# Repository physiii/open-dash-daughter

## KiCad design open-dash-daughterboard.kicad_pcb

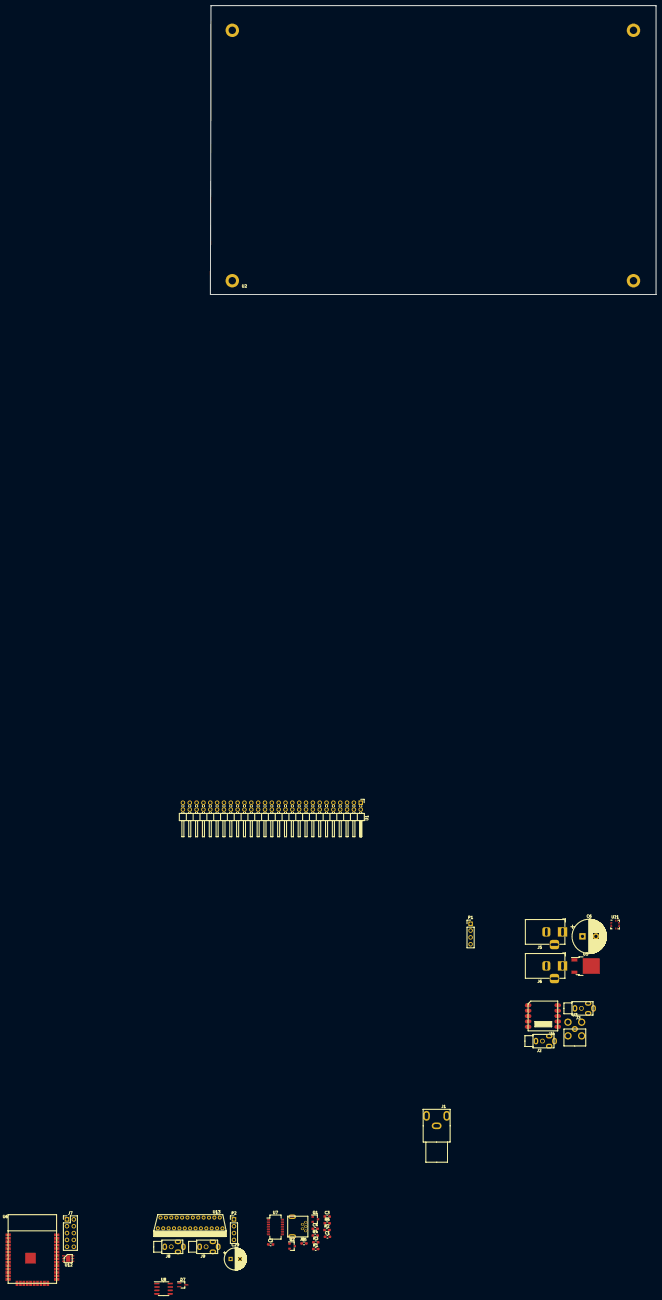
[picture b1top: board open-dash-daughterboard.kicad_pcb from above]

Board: 2 copper layers, 165.5 x 107.3 mm, 37 parts (0 on the bottom side), 41 nets, no tracks yet.

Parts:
C1, C2: C_47pF; C_0603_1608Metric_Pad1.05x0.95mm_HandSolder
C3, C5: C_0.1uF; C_0603_1608Metric_Pad1.05x0.95mm_HandSolder
C4: C_4.7uF; C_0603_1608Metric_Pad1.05x0.95mm_HandSolder
C6: C_1000uF; CP_Radial_D12.5mm_P5.00mm
C29: 470uF; CP_Radial_D8.0mm_P3.50mm
D7: PESD1CAN; SOT-323_SC-70_Handsoldering
J1: RCA-PJRAN1X1U04X
J2, J3, J8, J9: AudioJack4_TTRS; AudioConn-SJ1-2503A
J4: USB_MINI_B; USB-mini-B-0548190519
J5, J6: Barrel_Jack_OD5.5_ID2.5; BarrelJack_OD5.5_ID2.5
J7: Conn_02x05_Odd_Even; PinHeader_2x05_P2.54mm_Vertical
P1, P2: CONN_01X04; PinHeader_1x04_P2.54mm_Vertical
Q1: Q_NPN_BCE; SOT-23
Q2: Q_PNP_BCE; SOT-23
R1, R2: R_27; R_0603_1608Metric_Pad1.05x0.95mm_HandSolder
R3, R4: R_10k; R_0603_1608Metric_Pad1.05x0.95mm_HandSolder
R6: R_4K7; R_0603_1608Metric_Pad1.05x0.95mm_HandSolder
U1: TE-AUTO-CONN-52; PinHeader_2x27_P2.54mm_Horizontal
U2: radio-housing-mounts
U3: ANTENNA-COAX-AUTO; ANTENNA-AUTO- 638817-4
U4: RDA5807M
U5: REG-3.3v; TO-252-2
U6: ESP-WROOM-32
U7: FT231XS; SSOP-20_3.9x8.7mm_P0.635mm
U8: MCP2551-I_SN; SOIC-8_3.9x4.9mm_P1.27mm
U12: SI7020-A20
U13: TDA7851F; Flexiwatt25-V
U?1: ACS711; ACS711KEXLT-15AB-T

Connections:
/3V3: P1.2, U4.5, U5.2, U6.2, U12.5, U?1.12
/5V: C4.1, C5.1, P1.3, U5.3, U7.15, U8.3
/BATTERY: C6.1, C29.2, P1.4, U1.44, U?1.1
/CAMERA+: J1.2, J1.3, U1.31
/CAMERA-: J1.1, U1.32
/CAN+: D7.2, U1.2, U8.7
/CAN-: D7.1, U1.12, U8.6
/CAN_RX: U6.26, U6.28, U8.4
/CAN_TX: U6.29, U8.1
/FM Radio/AMF_Antenna: J3.2, J3.3, U3.1, U4.8
/FM Radio/L_FM: J2.2, J2.3, U4.7
/LF+: U1.47, U13.9
/LF-: U1.51, U13.7
/LR+: U1.48, U13.17
/LR-: U1.52, U13.19
/PROG: J7.3, Q2.2, U6.25
/RF+: U1.46, U13.5
/RF-: U1.50, U13.3
/RR+: U1.45, U13.21
/RR-: U1.49, U13.23
/RXD: J7.2, U6.34, U7.4
/SCL: J7.6, U4.2, U6.33, U12.6
/SDA: J7.8, U4.1, U6.31, U12.1
/TXD: J7.4, U6.35, U7.20
/USB interface/3V3OUT: C3.1, U7.3, U7.14
/USB interface/DTR: Q2.3, R4.2, U7.1
/USB interface/RTS: Q1.3, U7.2
/USB interface/USBDM: C1.1, J4.3, R1.2
/USB interface/USBDP: C2.1, J4.2, R2.2
/USB interface/VBUS: J4.1, R6.2
/USB interface/VSENSE: R6.1, U7.18
/audio amplifier/IN1: J8.2, J8.3, P2.4
/audio amplifier/IN2: J8.4, P2.3
/audio amplifier/IN3: J9.2, J9.3, P2.2
/audio amplifier/IN4: J9.4, P2.1
/microcontroller/FACT: J7.5, U6.13
/microcontroller/SOFT_POWER: J7.1, U6.14
GND: C1.2, C2.2, C3.2, C4.2, C5.2, C6.2, C29.1, D7.3, J2.1, J3.1, J3.4, J4.5, J5.2, J5.3, J6.2, J6.3, J7.9, J7.10, J8.1, J9.1, P1.1, U1.33, U1.43, U3.2, U4.6, U5.1, U6.1, U7.6, U7.16, U8.2, U12.2, U13.1, U13.13, U?1.5
unnamed: Q2.1, R3.2
unnamed: R1.1, U7.12
unnamed: R2.1, U7.11

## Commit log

2018-02-08 initial commit, added initial layout and datasheets for esp32 and CM108AH
2018-02-20 added initial layout
2018-02-22 added some libraries
2018-02-23 merged smart regulator with open-dash-daughter
2018-03-22 merged in smart regulator
2018-04-01 rearrange files/dir
2018-04-02 Ethan Initial Commit
    Copy of power section from smart-regulator
2018-04-02 Micro and Environment Schematic Copy
    Copied over the microcontroller and environment sheets from smart-regulator project. Also modified the power section.
2018-04-03 change branch
2018-04-03 Power Schematic Update
    Test commit and minior power schematic update.
2018-04-03 Backup Before SEPIC Design
2018-04-04 Component Updates in Power Section
2018-04-05 Updated Power Schematic
    Power Schematic Updated for 3.3V, 5V, and 8V Buck Regulators. All regulator parts have correct footprints and selected components.
    Prelim orgainization of PCB - grouped parts by section.
2018-04-05 Update Power Schematic and directed parts to open-automation library
    Change 3.3V and 5V buck regulator to adjustable chip version.
    Directed multiple parts from -cache.lib to open-automation.lib.
2018-04-06 Schematic Work on Audio Amp
    Audio amplifier implemented with selected components and footprints.
2018-04-06 Removed Light Sensor from Enviornment Schematic
2018-04-10 updated to v5 kicad
2018-04-12 finished updating libraries
2018-04-12 cleaned up some merge errors
2018-04-12 cleaning up repo
2018-04-12 latest and greatest, started canbus schematic
2018-04-17 added thermometer and switches for programming esp8299/esp32
2018-04-17 minor mods
2018-04-17 added GPS module, GPS will be on a carrier board and will plug into the daughter board.
2018-04-17 Backup before switching to lawrence-test branch
    Schematic library has issues after updating to KiCad V5.
2018-04-18 Revert "Backup before switching to lawrence-test branch"
    This reverts commit 5eeefb6d84a8db9381deb81c77fe1ec3b29fea69.
2018-04-18 Revert "Merge branch 'lawrence_test' into ethan"
    This reverts commit 4dccd689ac590a7d6c1598150e10b9b87c6b396b, reversing
    changes made to 5eeefb6d84a8db9381deb81c77fe1ec3b29fea69.
2018-04-18 Revert "Revert "Merge branch 'lawrence_test' into ethan""
    This reverts commit 6eb6401587b4cfce8c2da15c6df37be90675c3d0.
2018-04-18 Revert "added GPS module, GPS will be on a carrier board and will plug into the daughter board."
    This reverts commit f32f9f36995d7517ca6e5476fe45c3fadeca4b65.
2018-04-18 Revert "minor mods"
    This reverts commit 9cdac2227bb00ba5c1e83bbc5802a50bbe9e1756.
2018-04-18 Fixed Ethan Branch to actually merge "lawrence_test" branch
    Had some clinfict issues that were handeled incorrectly. Problems now fixed.
2018-04-18 Implemented CANBUS circuitry
    Implemented CANBUS circuitry based off sparkfun CAN-BUS Shield DEV-1326. Footprints and parts selected.
2018-04-19 merged ethans changes
2018-04-19 added connector in bom
2018-04-19 started AM/FM module, added datasheets
2018-04-19 FM Radio schematic in process
2018-04-19 implemented rough draft of FM circuit
2018-04-19 added GPS sheet and part, first draft needs further review
2018-04-20 added canbus info
2018-04-23 update ground symbols
2018-04-26 dangling commit
2018-04-26 added pinout for wireharness and canbus library
2018-04-26 updated BOM with RF AM/FM connectors and added connector pinout descriptions in Stereo wiring.ods
2018-04-26 updated wiring list
2018-04-26 added connector interface
2018-04-26 adding and cleaning lables
2018-04-27 add MCP2551 datasheet and ESP32-MCP2551 wiring table and picture
2018-04-27 demo esp32 canbus capture based on http://www.barth-dev.de/can-driver-esp32/
2018-04-27 FM/AM Radio Section Schematic Work and Parts Selection
2018-04-27 Added usb-audio interface schematic
2018-05-01 dummy ids for key on/off events with 30-second shutdown timer
2018-05-01 Slight re-arrangment, and added datasheets for potential video options.
2018-05-02 can-capture program to print frames with sequence # and ticks; scripts+captures for ignition and lock-unlock-door
2018-05-02 separate vehicle power monitor project from can capture project (still untested and with dummy key on/off CAN IDs)
2018-05-05 initial commit of unmodified ws2812-demo code, basis for Dolphin LED modifications
2018-05-06 (untested) ESP32 program to receive JSON LED state change description from BT SPP client and set light status (WS2812 code didn't work)
2018-05-06 attempt to manually feed WS2812 timings to RMT driver
2018-05-07 Static CAN messages
    Just a dump of all CAN message labels being broadcast whose contents do not change. First dump is with engine on, second with engine off. Only one additional message label appears to stop changing wi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
2018-05-07 update ws2812 timings; looks good on scope
2018-05-08 seem to be able to control the lights now
2018-05-08 remove some old things
2018-05-08 bounce the lights back and forth
2018-05-08 light up the whole strip
2018-05-11 added mainboard-interface
2018-05-11 organized bus connections
2018-05-11 organizing
2018-05-11 update net
2018-05-11 Fixed description of one CAN label
2018-05-11 Updated with numerous new CAN messages 5-12-18
2018-05-15 print messages as strings
2018-05-15 added footprints and merged from main branch and
2018-05-15 added new parts and started layout
2018-05-16 join working bt/spp and ws8212 code into one dolphin light demo
2018-05-18 ignore build dir
2018-05-18 Create references
2018-05-21 output raw canid and message
2018-05-22 Matt's Python script for reading CAN data
    This is ugly and not-production-ready......just the script I cooked up to make sense of CAN messages, but perhaps some of the logic would be useful in the project's main CAN code.
2018-05-22 New data 5-22-18 for side & back doors, one correction
    I've discovered there is apparently no data tied to key insertion state, and I've corrected that documentation in the spreadsheet. - Matt
2018-05-27 made kicad-parts path relative
2018-06-01 receive strings from serial port in preparation for communicating with dash via JSON
2018-06-01 make this string demo runnable
2018-06-02 start building daughter state machine for can-triggered dash power on/off
2018-06-02 incomplete changes to pass messages between daughter and dash
2018-06-02 debug stuff
2018-06-02 switch back to real non-debug build
2018-06-03 start refactoring this, no message queues and only two tasks (not successfully run)
2018-06-03 wait after power up/down status; dashsim.js to simulate the dash for debug purposes (use instead of make monitor)
2018-06-04 Working on it
2018-06-04 Added node+module folder to root file and package.json with serialport
2018-06-04 Corrected spacing on dashsim.js and some constants and variables
2018-06-05 rearranged traces
2018-06-05 molex fix
2018-06-05 added BOM
2018-06-05 final update silk screen
2018-06-06 finalizing board
2018-06-07 update CAN message JSON schema; correct _DEBUG logging
2018-06-07 make debug for non-production non-JSON output, and make verbose to print all non-RTR CAN frames
2018-06-07 parts swap
2018-06-09 sdkconfig 921600 baud to avoid frame drop
2018-06-09 blink in a separate task
2018-06-13 testing boot functionality
2018-06-15 added softpower circuit
2018-06-20 inductor update
2018-06-20 refactoring
2018-06-20 corrections day 1
2018-06-22 corrections
2018-06-25 schematic final
2018-06-25 audio
2018-06-25 almost there
2018-06-26 updated corrections
2018-06-26 start layout
2018-06-27 layout needs Payne Approval
2018-06-28 adjustment
2018-06-28 final layout
2018-06-28 last minute
2018-06-28 rearranged components
2018-06-28 traces
2018-06-29 finshed traces 1
2018-06-29 pcb mostly complete
2019-04-21 starting next revision
2019-04-22 starting next revision - 0.2
2019-04-24 finished schematic, starting layout
2019-04-28 Finished layout (v0.2), sent to board house
2019-05-09 0.2 revisions
2019-05-10 3.5 audio connectors, FM and USB mods
2019-05-11 sent 0.2 revision to pcb house
2019-05-14 modified adapter, TE 52
2019-05-16 using mouser parts because digkey BOM broke
2019-05-25 power commands
2019-06-21 sent to board house
2020-11-07 starting vette revision
2020-11-14 Wrote J1850 driver. Testing receive.
2020-11-14 j1850 testing
2020-11-15 Passing through j1850 codes in json object.
2020-11-19 Printing test j1850 data
